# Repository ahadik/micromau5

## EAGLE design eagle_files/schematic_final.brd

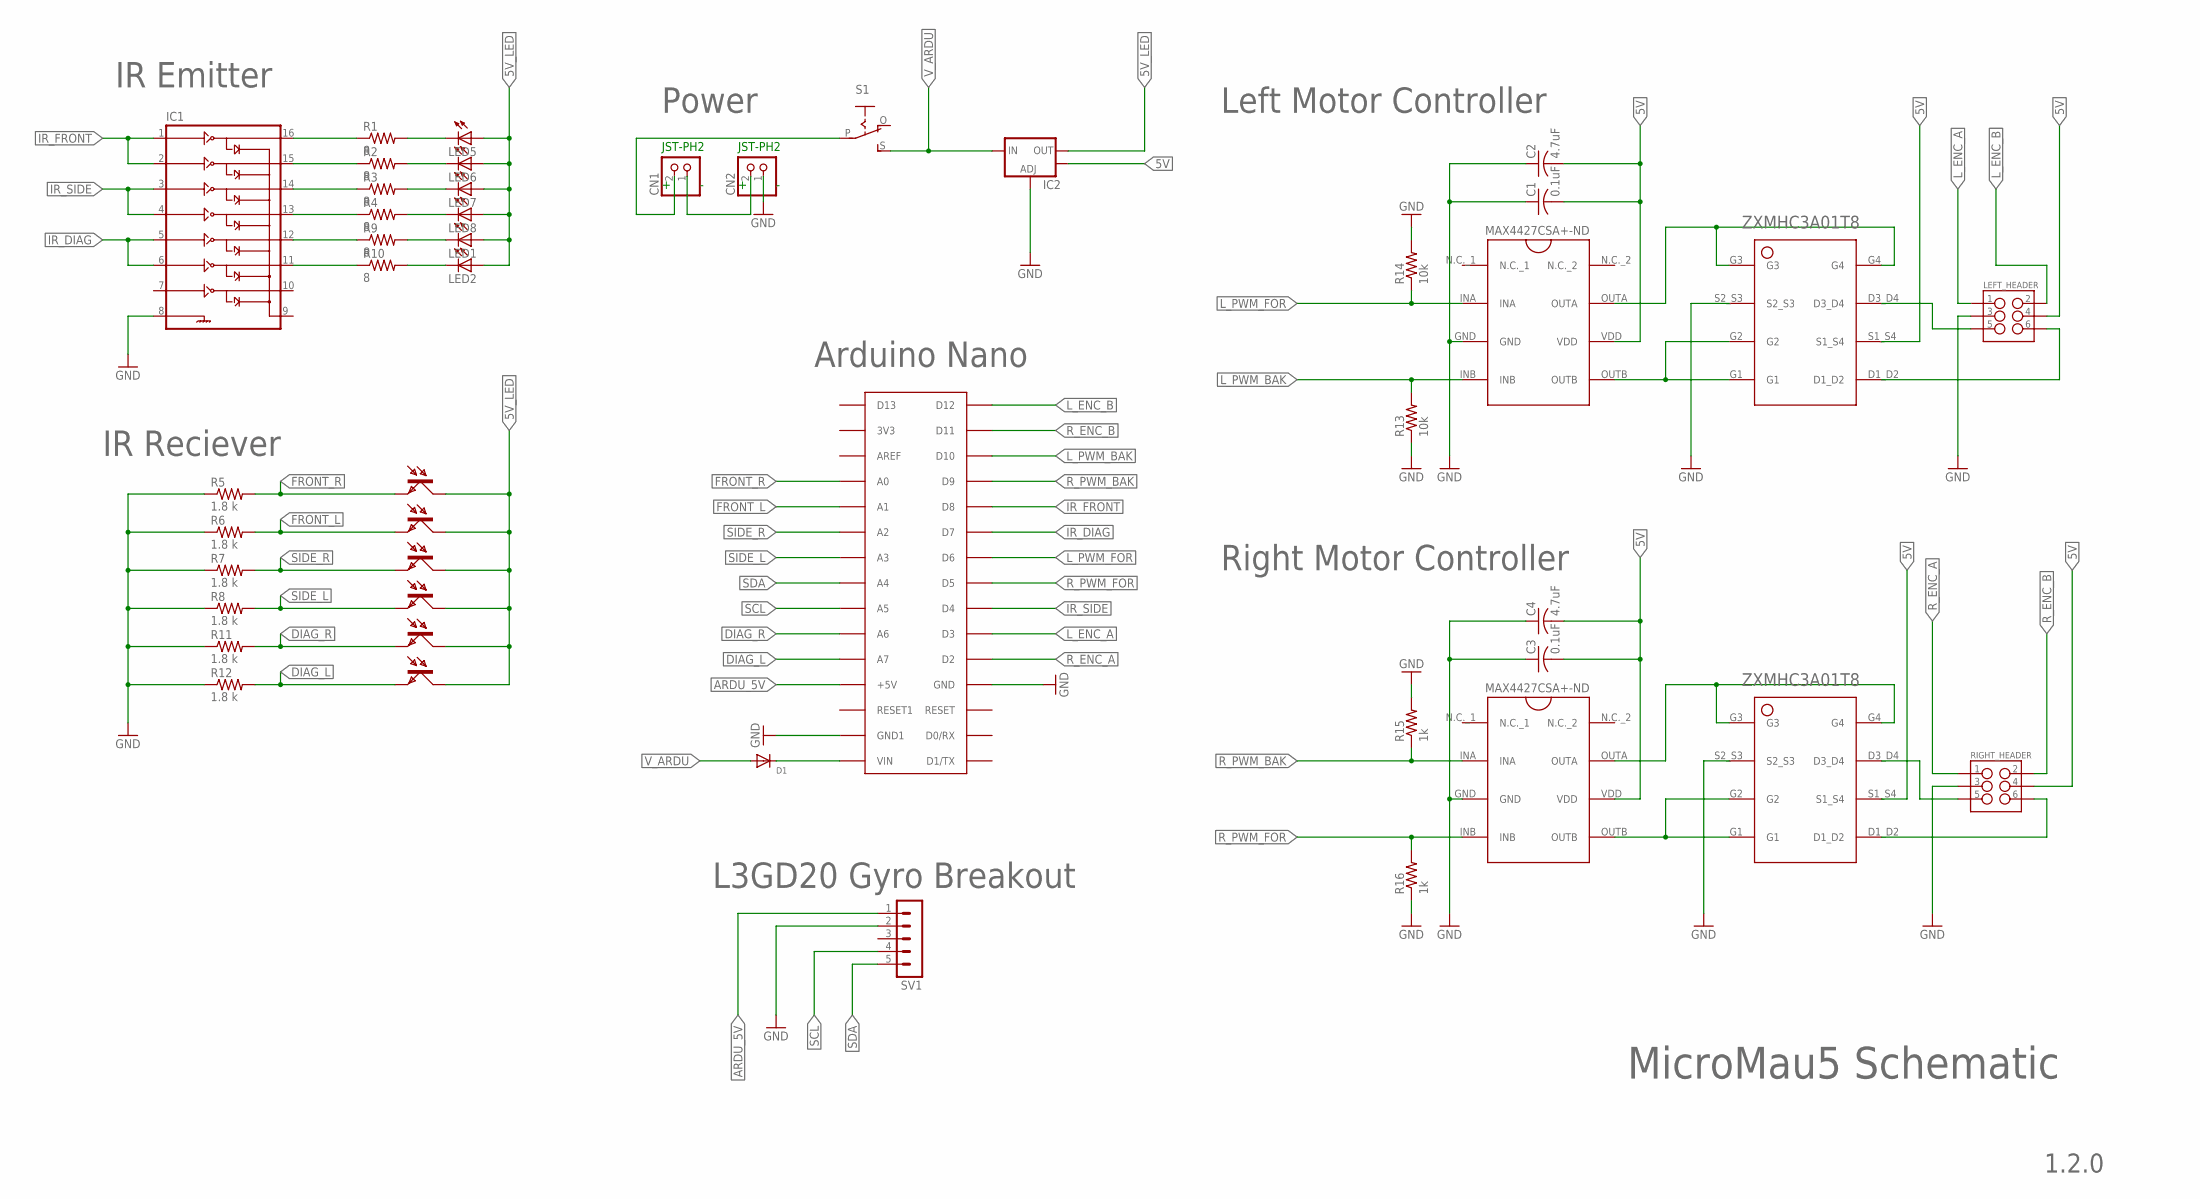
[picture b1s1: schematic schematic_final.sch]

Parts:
C1, C3: 0.1uF; C0805
C2, C4: 4.7uF; C0805
CN1, CN2: JST_2PIN-THM; JST-PH-2-THM
D1: DIODESOD-123; SOD-123
IC1: IC_ULN2003-TSSOP-16; TSSOP-16
IC2: V_REG_LM1117SOT223; SOT223
LED1, LED2, LED5, LED6, LED7, LED8: LED5MM
LEFT_HEADER: M03X2SHROUD; 2X3-SHROUDED
R1, R2, R3, R4, R9, R10: 8; M0805
R5, R6, R7, R8, R11, R12: 1.8 k; R0805
R13, R14: 10k; R0805
R15, R16: 1k; R0805
RIGHT_HEADER: M03X2SHROUD; 2X3-SHROUDED
S1: EG1218S; EG1218
SV1: MA05-1
T1, T2, T3, T4, T5, T6: BPX81
U$1, U$4: MAX4427CSA+-ND
U$2, U$5: ZXMHC3A01T8
U$3: ARDUINONANO; PDIP-32

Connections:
5V: C1.2, C2.2, C3.2, C4.2, IC2.4 (OUT), LEFT_HEADER.4, RIGHT_HEADER.4, U$1.VDD, U$2.S1_S4, U$4.VDD, U$5.S1_S4
5V_LED: IC2.2 (OUT), LED1.A, LED2.A, LED5.A, LED6.A, LED7.A, LED8.A, T1.C, T2.C, T3.C, T4.C, T5.C, T6.C
ARDU_5V: SV1.1, U$3.+5V
DIAG_L: R12.2, T6.E, U$3.A7
DIAG_R: R11.2, T5.E, U$3.A6
FRONT_L: R6.2, T3.E, U$3.A1
FRONT_R: R5.2, T2.E, U$3.A0
GND: C1.1, C2.1, C3.1, C4.1, CN2.1 (2), IC1.8 (GND), IC2.1 (ADJ), LEFT_HEADER.3, R5.1, R6.1, R7.1, R8.1, R11.1, R12.1, R13.1, R14.2, R15.2, R16.1, RIGHT_HEADER.3, SV1.2, U$1.GND, U$2.S2_S3, U$3.GND, U$3.GND1, U$4.GND, U$5.S2_S3
IR_DIAG: IC1.5 (5B), IC1.6 (6B), U$3.D7
IR_FRONT: IC1.1 (1B), IC1.2 (2B), U$3.D8
IR_SIDE: IC1.3 (3B), IC1.4 (4B), U$3.D4
L_ENC_A: LEFT_HEADER.1, U$3.D3
L_ENC_B: LEFT_HEADER.2, U$3.D12
L_PWM_BAK: R13.2, U$1.INB, U$3.D10
L_PWM_FOR: R14.1, U$1.INA, U$3.D6
unnamed: U$1.OUTB, U$2.G1, U$2.G2
unnamed: LEFT_HEADER.5, U$2.D3_D4
unnamed: U$1.OUTA, U$2.G3, U$2.G4
unnamed: LEFT_HEADER.6, U$2.D1_D2
unnamed: CN1.1 (2), CN2.2 (1)
unnamed: CN1.2 (1), S1.P
unnamed: U$4.OUTB, U$5.G1, U$5.G2
unnamed: U$4.OUTA, U$5.G3, U$5.G4
unnamed: RIGHT_HEADER.5, U$5.D3_D4
unnamed: RIGHT_HEADER.6, U$5.D1_D2
unnamed: IC1.16 (1C), R1.1
unnamed: IC1.15 (2C), R2.1
unnamed: IC1.14 (3C), R3.1
unnamed: IC1.13 (4C), R4.1
unnamed: LED5.K (C), R1.2
unnamed: LED6.K (C), R2.2
unnamed: LED7.K (C), R3.2
unnamed: LED8.K (C), R4.2
unnamed: IC1.12 (5C), R9.1
unnamed: IC1.11 (6C), R10.1
unnamed: LED1.K (C), R9.2
unnamed: LED2.K (C), R10.2
unnamed: D1.C, U$3.VIN
R_ENC_A: RIGHT_HEADER.1, U$3.D2
R_ENC_B: RIGHT_HEADER.2, U$3.D11
R_PWM_BAK: R15.1, U$3.D9, U$4.INA
R_PWM_FOR: R16.2, U$3.D5, U$4.INB
SCL: SV1.4, U$3.A5
SDA: SV1.5, U$3.A4
SIDE_L: R8.2, T4.E, U$3.A3
SIDE_R: R7.2, T1.E, U$3.A2
V_ARDU: D1.A, IC2.3 (IN), S1.S

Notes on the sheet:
L3GD20 Gyro Breakout
JST-PH2
1.2.0
MicroMau5 Schematic
IR Emitter
IR Reciever
Power
Arduino Nano
Left Motor Controller
Right Motor Controller

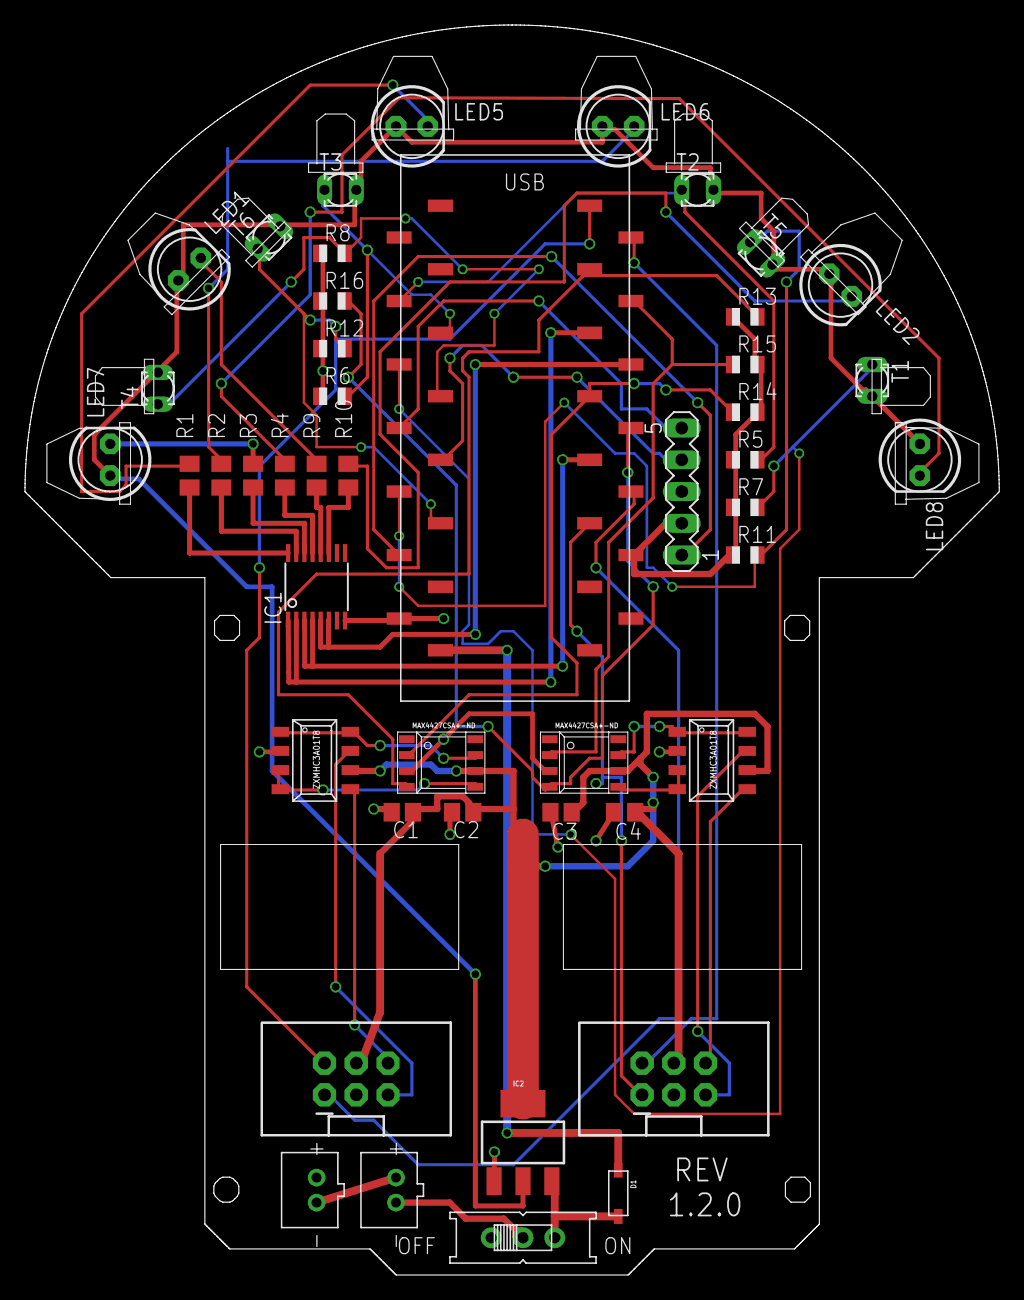
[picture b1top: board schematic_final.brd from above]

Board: 4 copper layers, 77.9 x 100.0 mm, 46 parts (0 on the bottom side), 47 nets.

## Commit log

2013-11-22 Adding Processing/Arduino file writing code
2013-11-23 This is a commit by Tristan
2013-11-23 test
2013-11-23 remove test
2013-11-23 adding pwm code
2013-12-06 Adding motor mount design documents
2013-12-06 Adding final cut
2014-01-04 adding Java code for prototype maze solver
2014-01-04 Resolving some inconsistencies
2014-01-04 resolving inconcsistencies
2014-01-04 resolving inconsistencies
2014-01-04 readding Motor_Mount
2014-01-06 Adding initialization of distance matrix and preliminary functions for navigation and maze discovery
2014-01-07 Adding code for implemented flood fill algorithm.
2014-01-07 refactoring code to place maze solver in a separate class
2014-01-08 Reworked code so MazeSolver as a separate class correctly finds the shortest path to the center of a maze accessing only the points of the maze that it visits.
2014-01-09 IT WORKS! Finally adding code that properly infers the values of unvisited cells by rescoring cells adjacent to cells currently visited. This allows for a functioning flood fill algorithm.
2014-01-10 split rendering functions into render class
2014-01-10 Adding Parser class to read in custom mazes created as text files
2014-01-10 adding most recent Parser code
2014-01-16 First git commit at 10,000 ft! Added code to allow reading of maze from text file for controlled testing
2014-02-09 adding board layouts
2014-02-09 adding updated motor mount AI file
2014-02-10 adding updated and new AI files for motor mount
2014-02-14 adding files for final iteration of motor mount and for first iteration of wheels
2014-02-14 updating wheel file
2014-02-21 adding most recent ai files
2014-02-22 adding updated illustrator files for wheels and motor mounts
2014-03-05 arduinooo
2014-03-09 Adding base code files for ir control
2014-03-10 Kevin's arduino
2014-03-10 updated IR code
2014-03-10 restructing Arduino code so all is under 'arduino/' directory
2014-03-18 adding first prototype Arduino code for ir_sensors (test_code)
2014-03-19 updating IR Code so that pin outs are accurate with fucked up board
2014-03-27 moving IR code to arduino directory
2014-03-27 minor changes to ir code
2014-03-27 adding updated flood_fill code
2014-03-28 adding changes to test_code and callibrator files
2014-03-28 adding eagle schematic and layout files
2014-03-28 adding eagle libraries
2014-03-28 adding images of schematic and layout
2014-03-29 updated ground connections
2014-03-29 updated schematic and layout
2014-03-29 Adding final modifications to IR library, and an IR readme. Began micromau5 sketch to serve as the main sketch for robot
2014-03-29 tiny modification to micromau5.ino
2014-03-31 updated board
2014-04-01 made lots of changes :)
2014-04-02 encoders and stuff
2014-04-06 oops
2014-04-06 Updating Solver code
2014-04-07 adding ported flood fill code and new entry struct to repository
2014-04-08 updating master
2014-04-08 removing duplicate solver files from master branch
2014-04-08 mering flood_fill
2014-04-08 motor code (look at motor_pid)
2014-04-08 Updated Captain's Log with detailed maze IR callibration info
2014-04-10 updated gyro code
2014-04-10 Adding Arduino code for motor control and gyro reading
2014-04-10 micromau5.ino has working gyro code. instruction struct added
2014-04-11 adding code for turning robot
2014-04-11 Added code for executing turning instructions
2014-04-11 Added in damping factor for driving straight
2014-04-11 Added updated steering code
2014-04-11 Changed code to work with bytes. Small bug fixes for maze instantiation

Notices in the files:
parts and their libraries:
SparkFun-Connectors: Licensing: CC v3.0 Share-Alike You are welcome to use this library for commercial purposes.
SparkFun-PowerIC: Licensing: Creative Commons ShareAlike 4.0 International - https://creativecommons.org/licenses/by-sa/4.0
